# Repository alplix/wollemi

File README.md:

# Wollemi

> **Private for now.** The repository will be opened to the public once the design is complete. No licence has been applied yet; the plan (`docs/licensing.md`) is CERN-OHL-S-2.0 for hardware,
> Apache-2.0 for software and CC-BY-4.0 for documents. Analysis-level design only: no hardware exists, nothing here is qualified for flight, and every number is an engineering estimate.

Wollemi is an open, modular, fully documented small-satellite **platform** and a first mission built on it: a science-first, long-life **12U observatory** with a tiered 50-year survival design.
Everything is generated from configuration files and checked by tools, so a derived mission is a configuration change plus new cards.

*Türkçe özet:* Wollemi, açık kaynak, modüler bir küçük uydu platformu ve üzerine kurulu ilk görev: uzun ömürlü, bilim öncelikli 12U gözlemevi. Tasarım analiz düzeyinde tamamlandı (donanım yok);
her sayı config dosyalarından üretilen araçlarla doğrulanıyor. Depo şimdilik özel, tasarım olgunlaşınca herkese açılacak.

## Where things stand

The design is **complete at analysis level**: requirements, architecture, CAD with interference checks, power/thermal/attitude/orbit/structure analyses, protocol and firmware core with tests,
electronics interface (KiCad, DRC clean), FMEA, test plan, operations concept, cost and schedule. Start with **`docs/sdd.md`** (system design document) and **`docs/status.md`** (latest regression).
What is missing is physical: vendor data, schematics of the functional cards, prototypes, tests, a launch and an operator. See `docs/plan.md`, `docs/risks.md` and `docs/cost.md`.

| At a glance | Value |
|---|---|
| Form | 12U CubeSat envelope, 2 x 2 x 3 cell grid around a central spine, notched 100 x 100 mm cards |
| Mass / power | about 16.8 kg of 24 kg; 58 W sun-biased, 28 W tumbling, 3 W safe-mode load |
| Science | ~26 instruments: telescope (5 m class) + hyperspectral, thermal IR, magnetometer, particles, X-ray/UV, TSI, VLF, GRB, dosimetry, SEU/flash experiments |
| Compute | MSP430 supervisor, 2 x STM32H7, mass memory unit (8 x 128 GB, 6+2), Pi CM5, Jetson Orin Nano |
| Power | two LiFePO4 chains + independent survival chain, hardware-only protection |
| Propulsion | iodine electric thruster on the centre line, ~570 m/s available (about 190 m/s planned), drag sail |
| Verification | 47 requirements traced (see `docs/verification-matrix.md`); most checked automatically on every run; 29 planned tests |

## Documentation

| Topic | Read |
|---|---|
| Overview | `docs/sdd.md`, `docs/plan.md`, `docs/status.md` |
| Requirements and verification | `mission/requirements.md`, `docs/verification-matrix.md`, `docs/test-plan.md`, `docs/fmea.md`, `docs/risks.md` |
| Design | `docs/architecture.md`, `docs/layout.md`, `docs/structure.md`, `docs/icd.md`, `mechanical/README.md` |
| Power, thermal, attitude, propulsion | `docs/power-architecture.md`, `docs/eps-card.md`, `docs/thermal.md`, `docs/adcs.md`, `docs/propulsion.md`, `docs/orbit-and-debris.md` |
| Electronics, software, data | `docs/electrical-interface.md`, `docs/firmware-architecture.md`, `docs/protocol.md`, `docs/data-plan.md`, `docs/mission-simulation.md` |
| Operations and ground | `docs/ops-concept.md`, `docs/ground-station-kit.md`, `docs/longevity.md` |
| Context | `docs/sponsor-brief.md`, `docs/relay-policy.md`, `docs/prior-art.md`, `docs/design-identity.md`, `docs/decisions/`, `docs/outreach-led.md`, `docs/cost.md`, `docs/licensing.md`, `CREDITS.md` |

## Repository layout

| Path | Content |
|---|---|
| `configs/` | Single source of truth: science, geometry, layout, data, longevity, thermal, structure, cost (+ 2U/3U/6U variants) |
| `mission/` | Requirements, `traceability.toml` (requirement -> verification), `tests.toml` (planned tests), `fmea.toml` |
| `sim/` | Budgets, layout rules, balance, data, longevity, link, EPS, ADCS, thermal, structure, orbit lifetime, mission simulation, cost, LED visibility, live verification matrix |
| `mechanical/` | Voxel packing, parametric build123d assembly, interference/mass properties, STEP/STL/renders |
| `electronics/` | Connector pinout (single source), KiCad card template and 15-slot backplane strip (DRC clean), EPS diagram, EPS/survival card floor plans (DRC clean, not yet a schematic) |
| `protocol/` | Message definitions, C/Python/Kaitai Struct generators, tests (round trip, corruption, byte-exact C <-> Python, Kaitai model verified against a real compiler) |
| `firmware/` | Host-testable core: Ed25519 command authentication, modes, FDIR, command queue, A/B OTA (84 unit checks + signature cross-checks) |
| `groundstation/` | Pass prediction, contact plan, reference decoder, Kaitai Struct decoders for the whole protocol |
| `tools/` | `check_all.py` (whole regression), FMEA, test-plan and requirement checks, generators for the ICD and the SDD |
| `site/` | Draft project website (English), prepared but not published -- repository is still private (`site/README.md`) |

## Quick start

```
pip install build123d cryptography sgp4       # CAD kernel, signing tests, orbit propagation (numpy, scipy, pillow come with build123d); KiCad 10 optional for DRC
python tools/check_all.py                     # runs every analysis and test, writes docs/status.md   (--quick skips CAD, thermal and the verification matrix)
python sim/trace_check.py                     # live requirements verification matrix
python mechanical/wollemi_cad.py               # full CAD assembly and checks, exports into mechanical/out/
python tools/gen_sdd.py                       # regenerate the system design document
```

Requires Python 3.11+ and GCC for the firmware and protocol tests. The `sim/` tools use only the standard library unless noted.

## Status and next steps

Design freeze candidate v0 at analysis level. The decisions that shape everything next: choose the target (flight mission, flight-quality reference design, or the precursor path with a FlatSat and a balloon flight),
confirm the preferred orbit, and get vendor quotes and datasheets. Details in `docs/sdd.md` section 8.

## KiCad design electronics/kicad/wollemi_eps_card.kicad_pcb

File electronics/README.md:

# Electronics

| File | Role |
|---|---|
| `card_pinout.toml` | Single source for the WL-P and WL-D connector pinouts and the card outline |
| `gen_card.py` | Generates the KiCad card template and `pinout.md`, runs `kicad-cli` DRC (needs KiCad 10) |
| `kicad/wollemi_card_template.kicad_pcb` | 100 x 100 mm card with the 20 x 20 mm spine notch, 4 x M2.5 holes, edge-guide keep-outs, WL-P and WL-D connector placeholders with every net assigned |
| `kicad/wollemi_card_template.svg`, `_top.png` | Renders |
| `gen_backplane.py` | Generates the 15-slot passive backplane strip (one per column), runs `kicad-cli` DRC |
| `kicad/wollemi_backplane_strip.kicad_pcb` | Passive backplane strip: 15 card slots, WL-P/WL-D routing per chain, DRC clean |
| `gen_eps_card.py` | Generates function-block floor plans for the EPS-A/EPS-B and survival cards on the real card outline (`docs/eps-card.md`), runs `kicad-cli` DRC |
| `kicad/wollemi_eps_card.kicad_pcb`, `wollemi_survival_card.kicad_pcb` | Floor plans only: labelled placeholder blocks proving the partition fits the card, DRC clean; not a routed schematic |
| `eps_diagram.py` | Generates the EPS block diagram `eps_diagram.svg` |
| `pinout.md` | Generated pin tables |

```
python electronics/gen_card.py
python electronics/gen_backplane.py
python electronics/gen_eps_card.py
```

The card template has no routing yet: `unconnected_items` and generated-library warnings are silenced in its project file on purpose. Cards derived
from it must re-enable them. Connector footprints are placeholders (2-row, 1.27 mm pitch pads); replace with the vendor footprint once the
connector family is chosen (`docs/electrical-interface.md`).

Next: choose real parts and capture a routed schematic for the EPS and survival cards (`docs/eps-card.md`); a first functional (non-EPS) card schematic.

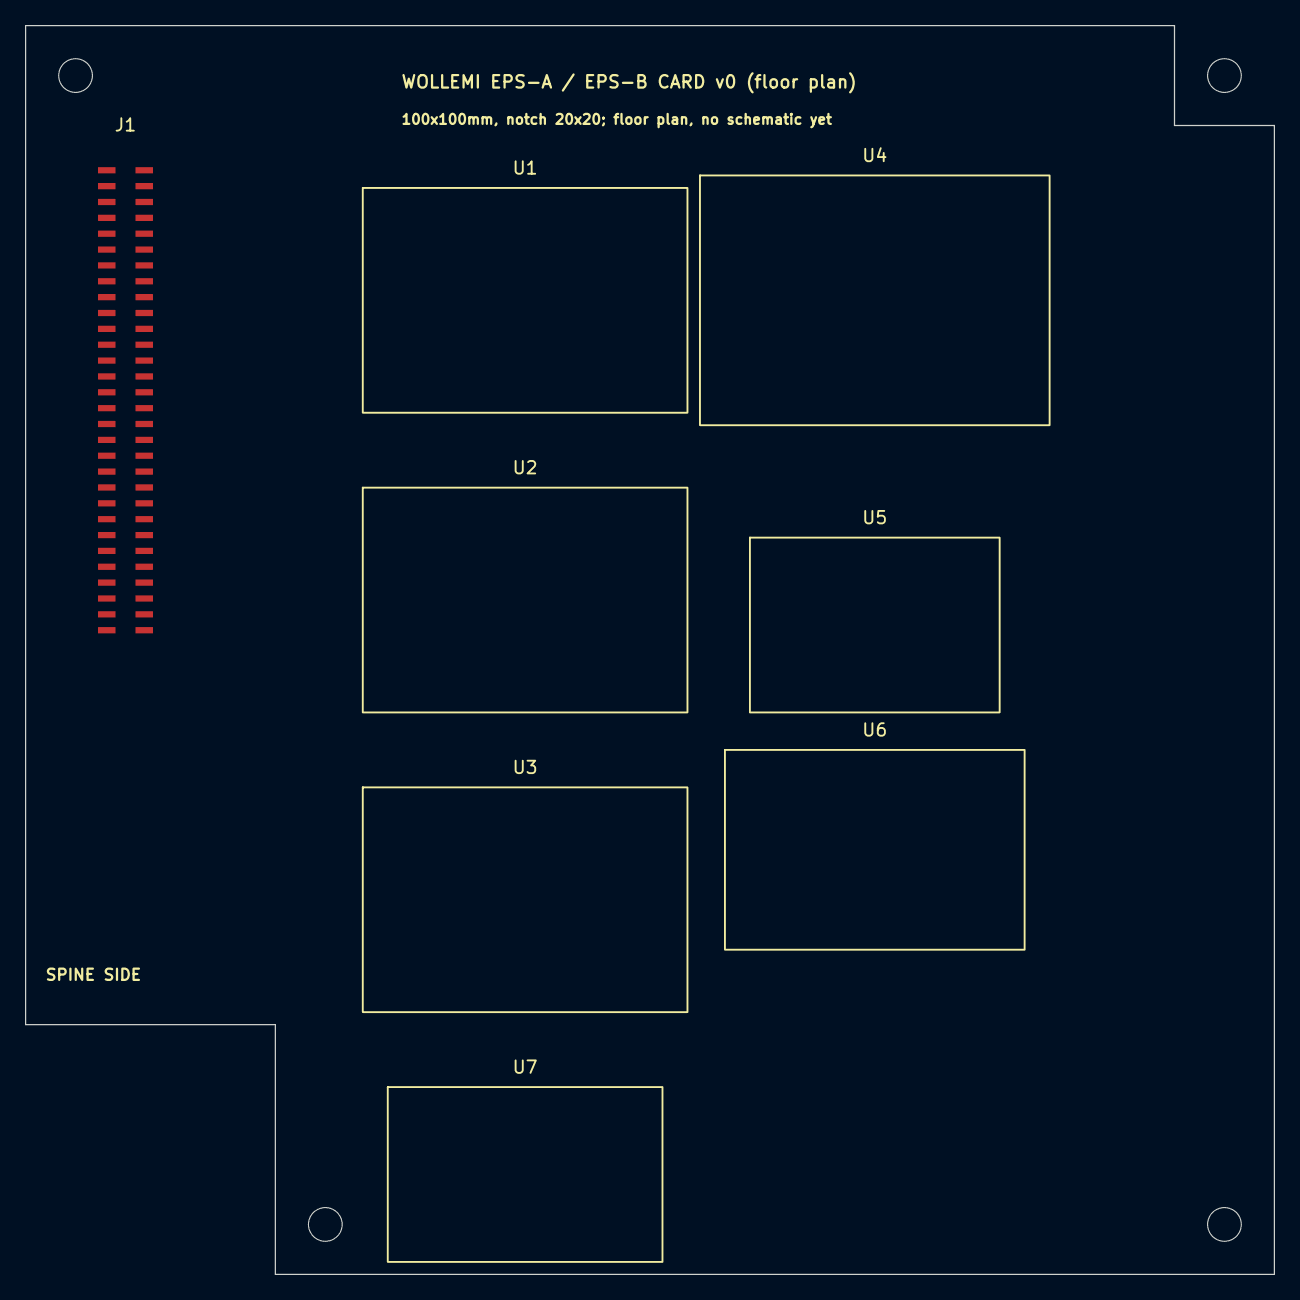
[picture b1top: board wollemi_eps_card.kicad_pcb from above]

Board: 4 copper layers, 100.0 x 100.0 mm, 12 parts (0 on the bottom side), 4 nets, no tracks yet.

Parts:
H: M2.5; MountingHole_2.7mm_M2.5
H#2, H#3, H#4: M2.5; MountingHole_2.7mm_M2.5
J1: WL-P; WL-P_placeholder
U1, U2, U3: LT8490; LT8490_placeholder
U4: BQ29209-Q1; BQ29209-Q1_placeholder
U5: LTC4359; LTC4359_placeholder
U6: TPS2597x; TPS2597x_placeholder
U7: STM32G0B1; STM32G0B1_placeholder

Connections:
GND: J1.11, J1.12, J1.15, J1.16, J1.19, J1.20, J1.23, J1.24, J1.27, J1.28, J1.39, J1.40, J1.45, J1.46, J1.51, J1.52
RSV: J1.54, J1.55, J1.56, J1.57, J1.58, J1.59, J1.60
VBAT_A: J1.1, J1.3, J1.5, J1.7, J1.9
VBAT_B: J1.2, J1.4, J1.6, J1.8, J1.10

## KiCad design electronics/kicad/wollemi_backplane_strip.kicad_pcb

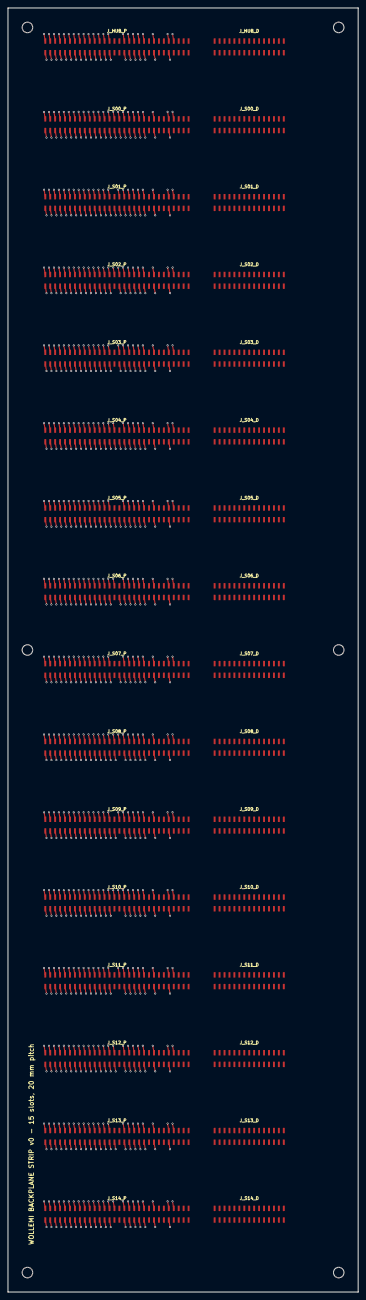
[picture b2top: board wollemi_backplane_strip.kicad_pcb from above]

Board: 6 copper layers, 90.0 x 330.0 mm, 38 parts (0 on the bottom side), 20 nets.

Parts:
H: M2.5; MountingHole_2.7mm_M2.5
H#2, H#3, H#4, H#5, H#6: M2.5; MountingHole_2.7mm_M2.5
J_HUB_D: WL-D; WL-D_backplane_placeholder
J_HUB_P: WL-P; WL-P_backplane_placeholder
J_S00_D, J_S01_D, J_S02_D, J_S03_D, J_S04_D, J_S05_D, J_S06_D, J_S07_D, J_S08_D, J_S09_D, J_S10_D, J_S11_D, J_S12_D, J_S13_D, J_S14_D: WL-D; WL-D_backplane_placeholder
J_S00_P, J_S01_P, J_S02_P, J_S03_P, J_S04_P, J_S05_P, J_S06_P, J_S07_P, J_S08_P, J_S09_P, J_S10_P, J_S11_P, J_S12_P, J_S13_P, J_S14_P: WL-P; WL-P_backplane_placeholder

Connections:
CAN_A_H: J_HUB_P.13, J_S00_P.13, J_S01_P.13, J_S02_P.13, J_S03_P.13, J_S04_P.13, J_S05_P.13, J_S06_P.13, J_S07_P.13, J_S08_P.13, J_S09_P.13, J_S10_P.13, J_S11_P.13, J_S12_P.13, J_S13_P.13, J_S14_P.13
CAN_A_L: J_HUB_P.14, J_S00_P.14, J_S01_P.14, J_S02_P.14, J_S03_P.14, J_S04_P.14, J_S05_P.14, J_S06_P.14, J_S07_P.14, J_S08_P.14, J_S09_P.14, J_S10_P.14, J_S11_P.14, J_S12_P.14, J_S13_P.14, J_S14_P.14
CAN_B_H: J_HUB_P.17, J_S00_P.17, J_S01_P.17, J_S02_P.17, J_S03_P.17, J_S04_P.17, J_S05_P.17, J_S06_P.17, J_S07_P.17, J_S08_P.17, J_S09_P.17, J_S10_P.17, J_S11_P.17, J_S12_P.17, J_S13_P.17, J_S14_P.17
CAN_B_L: J_HUB_P.18, J_S00_P.18, J_S01_P.18, J_S02_P.18, J_S03_P.18, J_S04_P.18, J_S05_P.18, J_S06_P.18, J_S07_P.18, J_S08_P.18, J_S09_P.18, J_S10_P.18, J_S11_P.18, J_S12_P.18, J_S13_P.18, J_S14_P.18
FAULT_N: J_HUB_P.38, J_S00_P.38, J_S01_P.38, J_S02_P.38, J_S03_P.38, J_S04_P.38, J_S05_P.38, J_S06_P.38, J_S07_P.38, J_S08_P.38, J_S09_P.38, J_S10_P.38, J_S11_P.38, J_S12_P.38, J_S13_P.38, J_S14_P.38
GND: J_HUB_P.11, J_HUB_P.12, J_HUB_P.15, J_HUB_P.16, J_HUB_P.19, J_HUB_P.20, J_HUB_P.23, J_HUB_P.24, J_HUB_P.27, J_HUB_P.28, J_HUB_P.39, J_HUB_P.40, J_HUB_P.45, J_HUB_P.46, J_HUB_P.51, J_HUB_P.52, J_S00_P.11, J_S00_P.12, J_S00_P.15, J_S00_P.16, J_S00_P.19, J_S00_P.20, J_S00_P.23, J_S00_P.24, J_S00_P.27, J_S00_P.28, J_S00_P.29, J_S00_P.30, J_S00_P.31, J_S00_P.32, J_S00_P.39, J_S00_P.40, J_S00_P.45, J_S00_P.46, J_S00_P.51, J_S00_P.52, J_S01_P.11, J_S01_P.12, J_S01_P.15, J_S01_P.16, J_S01_P.19, J_S01_P.20, J_S01_P.23, J_S01_P.24, J_S01_P.27, J_S01_P.28, J_S01_P.30, J_S01_P.31, J_S01_P.32, J_S01_P.39, J_S01_P.40, J_S01_P.45, J_S01_P.46, J_S01_P.51, J_S01_P.52, J_S02_P.11, J_S02_P.12, J_S02_P.15, J_S02_P.16, J_S02_P.19, J_S02_P.20, J_S02_P.23, J_S02_P.24, J_S02_P.27, J_S02_P.28, J_S02_P.29, J_S02_P.31, J_S02_P.32, J_S02_P.39, J_S02_P.40, J_S02_P.45, J_S02_P.46, J_S02_P.51, J_S02_P.52, J_S03_P.11, J_S03_P.12, J_S03_P.15, J_S03_P.16, J_S03_P.19, J_S03_P.20, J_S03_P.23, J_S03_P.24, J_S03_P.27, J_S03_P.28, J_S03_P.31, J_S03_P.32, J_S03_P.39, J_S03_P.40, J_S03_P.45, J_S03_P.46, J_S03_P.51, J_S03_P.52, J_S04_P.11, J_S04_P.12, J_S04_P.15, J_S04_P.16, J_S04_P.19, J_S04_P.20, J_S04_P.23, J_S04_P.24, J_S04_P.27, J_S04_P.28, J_S04_P.29, J_S04_P.30, J_S04_P.32, J_S04_P.39, J_S04_P.40, J_S04_P.45, J_S04_P.46, J_S04_P.51, J_S04_P.52, J_S05_P.11, J_S05_P.12, J_S05_P.15, J_S05_P.16, J_S05_P.19, J_S05_P.20, J_S05_P.23, J_S05_P.24, J_S05_P.27, J_S05_P.28, J_S05_P.30, J_S05_P.32, J_S05_P.39, J_S05_P.40, J_S05_P.45, J_S05_P.46, J_S05_P.51, J_S05_P.52, J_S06_P.11, J_S06_P.12, J_S06_P.15, J_S06_P.16, J_S06_P.19, J_S06_P.20, J_S06_P.23, J_S06_P.24, J_S06_P.27, J_S06_P.28, J_S06_P.29, J_S06_P.32, J_S06_P.39, J_S06_P.40, J_S06_P.45, J_S06_P.46, J_S06_P.51, J_S06_P.52, J_S07_P.11, J_S07_P.12, J_S07_P.15, J_S07_P.16, J_S07_P.19, J_S07_P.20, J_S07_P.23, J_S07_P.24, J_S07_P.27, J_S07_P.28, J_S07_P.32, J_S07_P.39, J_S07_P.40, J_S07_P.45, J_S07_P.46, J_S07_P.51, J_S07_P.52, J_S08_P.11, J_S08_P.12, J_S08_P.15, J_S08_P.16, J_S08_P.19, J_S08_P.20, J_S08_P.23, J_S08_P.24, J_S08_P.27, J_S08_P.28, J_S08_P.29, J_S08_P.30, J_S08_P.31, J_S08_P.39, J_S08_P.40, J_S08_P.45, J_S08_P.46, J_S08_P.51, J_S08_P.52, J_S09_P.11, J_S09_P.12, J_S09_P.15, J_S09_P.16, J_S09_P.19, J_S09_P.20, J_S09_P.23, J_S09_P.24, J_S09_P.27, J_S09_P.28, J_S09_P.30, J_S09_P.31, J_S09_P.39, J_S09_P.40, J_S09_P.45, J_S09_P.46, J_S09_P.51, J_S09_P.52, J_S10_P.11, J_S10_P.12, J_S10_P.15, J_S10_P.16, J_S10_P.19, J_S10_P.20, J_S10_P.23, J_S10_P.24, J_S10_P.27, J_S10_P.28, J_S10_P.29, J_S10_P.31, J_S10_P.39, J_S10_P.40, J_S10_P.45, J_S10_P.46, J_S10_P.51, J_S10_P.52, J_S11_P.11, J_S11_P.12, J_S11_P.15, J_S11_P.16, J_S11_P.19, J_S11_P.20, J_S11_P.23, J_S11_P.24, J_S11_P.27, J_S11_P.28, J_S11_P.31, J_S11_P.39, J_S11_P.40, J_S11_P.45, J_S11_P.46, J_S11_P.51, J_S11_P.52, J_S12_P.11, J_S12_P.12, J_S12_P.15, J_S12_P.16, J_S12_P.19, J_S12_P.20, J_S12_P.23, J_S12_P.24, J_S12_P.27, J_S12_P.28, J_S12_P.29, J_S12_P.30, J_S12_P.39, J_S12_P.40, J_S12_P.45, J_S12_P.46, J_S12_P.51, J_S12_P.52, J_S13_P.11, J_S13_P.12, J_S13_P.15, J_S13_P.16, J_S13_P.19, J_S13_P.20, J_S13_P.23, J_S13_P.24, J_S13_P.27, J_S13_P.28, J_S13_P.30, J_S13_P.39, J_S13_P.40, J_S13_P.45, J_S13_P.46, J_S13_P.51, J_S13_P.52, J_S14_P.11, J_S14_P.12, J_S14_P.15, J_S14_P.16, J_S14_P.19, J_S14_P.20, J_S14_P.23, J_S14_P.24, J_S14_P.27, J_S14_P.28, J_S14_P.29, J_S14_P.39, J_S14_P.40, J_S14_P.45, J_S14_P.46, J_S14_P.51, J_S14_P.52
I2C_SCL: J_HUB_P.41, J_S00_P.41, J_S01_P.41, J_S02_P.41, J_S03_P.41, J_S04_P.41, J_S05_P.41, J_S06_P.41, J_S07_P.41, J_S08_P.41, J_S09_P.41, J_S10_P.41, J_S11_P.41, J_S12_P.41, J_S13_P.41, J_S14_P.41
I2C_SDA: J_HUB_P.42, J_S00_P.42, J_S01_P.42, J_S02_P.42, J_S03_P.42, J_S04_P.42, J_S05_P.42, J_S06_P.42, J_S07_P.42, J_S08_P.42, J_S09_P.42, J_S10_P.42, J_S11_P.42, J_S12_P.42, J_S13_P.42, J_S14_P.42
KILL_N: J_HUB_P.37, J_S00_P.37, J_S01_P.37, J_S02_P.37, J_S03_P.37, J_S04_P.37, J_S05_P.37, J_S06_P.37, J_S07_P.37, J_S08_P.37, J_S09_P.37, J_S10_P.37, J_S11_P.37, J_S12_P.37, J_S13_P.37, J_S14_P.37
PPS_N: J_HUB_P.22, J_S00_P.22, J_S01_P.22, J_S02_P.22, J_S03_P.22, J_S04_P.22, J_S05_P.22, J_S06_P.22, J_S07_P.22, J_S08_P.22, J_S09_P.22, J_S10_P.22, J_S11_P.22, J_S12_P.22, J_S13_P.22, J_S14_P.22
PPS_P: J_HUB_P.21, J_S00_P.21, J_S01_P.21, J_S02_P.21, J_S03_P.21, J_S04_P.21, J_S05_P.21, J_S06_P.21, J_S07_P.21, J_S08_P.21, J_S09_P.21, J_S10_P.21, J_S11_P.21, J_S12_P.21, J_S13_P.21, J_S14_P.21
RESET_N: J_HUB_P.53, J_S00_P.53, J_S01_P.53, J_S02_P.53, J_S03_P.53, J_S04_P.53, J_S05_P.53, J_S06_P.53, J_S07_P.53, J_S08_P.53, J_S09_P.53, J_S10_P.53, J_S11_P.53, J_S12_P.53, J_S13_P.53, J_S14_P.53
SLOT_SEL0: J_HUB_P.33, J_S00_P.33, J_S01_P.33, J_S02_P.33, J_S03_P.33, J_S04_P.33, J_S05_P.33, J_S06_P.33, J_S07_P.33, J_S08_P.33, J_S09_P.33, J_S10_P.33, J_S11_P.33, J_S12_P.33, J_S13_P.33, J_S14_P.33
SLOT_SEL1: J_HUB_P.34, J_S00_P.34, J_S01_P.34, J_S02_P.34, J_S03_P.34, J_S04_P.34, J_S05_P.34, J_S06_P.34, J_S07_P.34, J_S08_P.34, J_S09_P.34, J_S10_P.34, J_S11_P.34, J_S12_P.34, J_S13_P.34, J_S14_P.34
SLOT_SEL2: J_HUB_P.35, J_S00_P.35, J_S01_P.35, J_S02_P.35, J_S03_P.35, J_S04_P.35, J_S05_P.35, J_S06_P.35, J_S07_P.35, J_S08_P.35, J_S09_P.35, J_S10_P.35, J_S11_P.35, J_S12_P.35, J_S13_P.35, J_S14_P.35
SLOT_SEL3: J_HUB_P.36, J_S00_P.36, J_S01_P.36, J_S02_P.36, J_S03_P.36, J_S04_P.36, J_S05_P.36, J_S06_P.36, J_S07_P.36, J_S08_P.36, J_S09_P.36, J_S10_P.36, J_S11_P.36, J_S12_P.36, J_S13_P.36, J_S14_P.36
SYNC_N: J_HUB_P.26, J_S00_P.26, J_S01_P.26, J_S02_P.26, J_S03_P.26, J_S04_P.26, J_S05_P.26, J_S06_P.26, J_S07_P.26, J_S08_P.26, J_S09_P.26, J_S10_P.26, J_S11_P.26, J_S12_P.26, J_S13_P.26, J_S14_P.26
SYNC_P: J_HUB_P.25, J_S00_P.25, J_S01_P.25, J_S02_P.25, J_S03_P.25, J_S04_P.25, J_S05_P.25, J_S06_P.25, J_S07_P.25, J_S08_P.25, J_S09_P.25, J_S10_P.25, J_S11_P.25, J_S12_P.25, J_S13_P.25, J_S14_P.25
VBAT_A: J_HUB_P.1, J_HUB_P.3, J_HUB_P.5, J_HUB_P.7, J_HUB_P.9, J_S00_P.1, J_S00_P.3, J_S00_P.5, J_S00_P.7, J_S00_P.9, J_S01_P.1, J_S01_P.3, J_S01_P.5, J_S01_P.7, J_S01_P.9, J_S02_P.1, J_S02_P.3, J_S02_P.5, J_S02_P.7, J_S02_P.9, J_S03_P.1, J_S03_P.3, J_S03_P.5, J_S03_P.7, J_S03_P.9, J_S04_P.1, J_S04_P.3, J_S04_P.5, J_S04_P.7, J_S04_P.9, J_S05_P.1, J_S05_P.3, J_S05_P.5, J_S05_P.7, J_S05_P.9, J_S06_P.1, J_S06_P.3, J_S06_P.5, J_S06_P.7, J_S06_P.9, J_S07_P.1, J_S07_P.3, J_S07_P.5, J_S07_P.7, J_S07_P.9, J_S08_P.1, J_S08_P.3, J_S08_P.5, J_S08_P.7, J_S08_P.9, J_S09_P.1, J_S09_P.3, J_S09_P.5, J_S09_P.7, J_S09_P.9, J_S10_P.1, J_S10_P.3, J_S10_P.5, J_S10_P.7, J_S10_P.9, J_S11_P.1, J_S11_P.3, J_S11_P.5, J_S11_P.7, J_S11_P.9, J_S12_P.1, J_S12_P.3, J_S12_P.5, J_S12_P.7, J_S12_P.9, J_S13_P.1, J_S13_P.3, J_S13_P.5, J_S13_P.7, J_S13_P.9, J_S14_P.1, J_S14_P.3, J_S14_P.5, J_S14_P.7, J_S14_P.9
VBAT_B: J_HUB_P.2, J_HUB_P.4, J_HUB_P.6, J_HUB_P.8, J_HUB_P.10, J_S00_P.2, J_S00_P.4, J_S00_P.6, J_S00_P.8, J_S00_P.10, J_S01_P.2, J_S01_P.4, J_S01_P.6, J_S01_P.8, J_S01_P.10, J_S02_P.2, J_S02_P.4, J_S02_P.6, J_S02_P.8, J_S02_P.10, J_S03_P.2, J_S03_P.4, J_S03_P.6, J_S03_P.8, J_S03_P.10, J_S04_P.2, J_S04_P.4, J_S04_P.6, J_S04_P.8, J_S04_P.10, J_S05_P.2, J_S05_P.4, J_S05_P.6, J_S05_P.8, J_S05_P.10, J_S06_P.2, J_S06_P.4, J_S06_P.6, J_S06_P.8, J_S06_P.10, J_S07_P.2, J_S07_P.4, J_S07_P.6, J_S07_P.8, J_S07_P.10, J_S08_P.2, J_S08_P.4, J_S08_P.6, J_S08_P.8, J_S08_P.10, J_S09_P.2, J_S09_P.4, J_S09_P.6, J_S09_P.8, J_S09_P.10, J_S10_P.2, J_S10_P.4, J_S10_P.6, J_S10_P.8, J_S10_P.10, J_S11_P.2, J_S11_P.4, J_S11_P.6, J_S11_P.8, J_S11_P.10, J_S12_P.2, J_S12_P.4, J_S12_P.6, J_S12_P.8, J_S12_P.10, J_S13_P.2, J_S13_P.4, J_S13_P.6, J_S13_P.8, J_S13_P.10, J_S14_P.2, J_S14_P.4, J_S14_P.6, J_S14_P.8, J_S14_P.10

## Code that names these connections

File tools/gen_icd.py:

"""Generate docs/icd.md (interface control document) from the live design data.

Usage: python tools/gen_icd.py
Every number in the tables is read from the configs or computed by the analysis tools, so the ICD cannot drift from the design.
"""
import json
import os
import sys
import tomllib

ROOT = os.path.dirname(os.path.dirname(os.path.abspath(__file__)))
sys.path.insert(0, os.path.join(ROOT, "sim"))
sys.path.insert(0, os.path.join(ROOT, "mechanical"))
import budget  # noqa: E402
import wollemi_cad as gc  # noqa: E402


def load(p):
    return tomllib.load(open(os.path.join(ROOT, p), "rb"))


def main():
    cfg = load("configs/12u_science.toml")
    geo = load("configs/12u_geometry.toml")
    st = load("configs/12u_structure.toml")
    data = load("configs/12u_data.toml")
    pin = load("electronics/card_pinout.toml")
    placement = json.load(open(os.path.join(ROOT, "mechanical", "out", "placement.json")))
    r = budget.compute(cfg)
    M, com, inertia = gc.mass_props(placement["placed"], cfg, False, geo)
    Md, comd, inertia_d = gc.mass_props(placement["placed"], cfg, True, geo)
    fr = geo["frame"]
    wg = geo["wings"]
    ox, oy, oz = fr["outer"]
    stack = wg["panels_per_wing"] * wg["panel"][2]
    span = 2 * (ox / 2 + wg["panels_per_wing"] * wg["panel"][0])
    safe = next(s for s in r["scenarios"] if s["safe"])["cons"]
    n_gkp = len(pin["gkp"]["pairs"]) * 2
    n_gkd = len(pin["gkd"]["pairs"]) * 2
    link = data["link"]

    L = []
    a = L.append
    a("# Interface control document (generated)")
    a("")
    a("Generated by `python tools/gen_icd.py` from the configs and analysis tools; do not edit by hand. Every value is a design value (analysis or estimate) unless a source is named;")
    a("the launch-provider values in section 6 are assumptions to be replaced by the provider's interface requirements document.")
    a("")
    a("## 1. Mechanical interfaces")
    a("")
    a("| Item | Value | Source |")
    a("|---|---|---|")
    a(f"| Form factor | 12U CubeSat, envelope {ox:.1f} x {oy:.1f} x {oz:.1f} mm, rails {fr['rail']} mm | `configs/12u_geometry.toml` |")
    a(f"| Mass at launch | {r['mass_kg']:.2f} kg (limit 24 kg) | `sim/budget.py` |")
    a(f"| Centre of mass (offset from the geometric centre) | ({com[0]:+.1f}, {com[1]:+.1f}, {com[2]:+.1f}) mm stowed; ({comd[0]:+.1f}, {comd[1]:+.1f}, {comd[2]:+.1f}) mm wings deployed | `mechanical/wollemi_cad.py` |")
    a(f"| Moments of inertia (kg m2) | stowed ({inertia[0]:.3f}, {inertia[1]:.3f}, {inertia[2]:.3f}); deployed ({inertia_d[0]:.3f}, {inertia_d[1]:.3f}, {inertia_d[2]:.3f}) | same |")
    a(f"| Stowed wing stack thickness | {stack:.1f} mm (allowed protrusion {fr['protrusion_limit']} mm), six hold-down posts per wing | `docs/structure.md` |")
    a(f"| External protrusions | patch antennas 4 mm; thruster nozzle flush; boom and UHF antenna stowed inside the envelope | CAD |")
    a(f"| Deployables | 2 wings x {wg['panels_per_wing']} panels ({wg['panel'][0]:.0f} x {wg['panel'][1]:.0f} x {wg['panel'][2]} mm, cells both faces), deployed span {span:.0f} mm; magnetometer boom and UHF antenna (lengths to be fixed) | CAD |")
    a(f"| Internal architecture | 2 x 2 x 3 cell grid, central spine 40 mm, notched card 100 x 100 mm (20 mm notch, 8 mm relief), 4 mm backplane gap | `docs/layout.md`, `docs/electrical-interface.md` |")
    a(f"| Number of modules | {len(placement['placed'])} placed with 0 interferences | CAD check |")
    a("")
    a("## 2. Electrical interfaces")
    a("")
    a("| Item | Value |")
    a("|---|---|")
    a("| Main bus | VBAT_A and VBAT_B, 2S LiFePO4 5.0 - 7.3 V (nominal 6.4 V); cards accept 4.5 - 8.6 V; every card has its own eFuse (trip 1.5x nominal) |")
    a(f"| Card connectors | WL-P {n_gkp} pins (power, CAN-FD A/B, PPS, SYNC, SLOT_ID, SLOT_SEL, KILL_N, FAULT_N, RESET_N, I2C, UART, SWD) and WL-D {n_gkd} pins (Ethernet, fast lanes), pitch {pin['card']['connector_pitch']} mm |")
    a("| Backplane | 15 slots plus hub per column, bussed signals daisy-chained, GND and battery planes (`electronics/gen_backplane.py`, DRC clean) |")
    a("| Battery packs | A and B: 2S2P 26650 LiFePO4, 42 Wh each; C: 5 Wh survival pack with independent charger |")
    a(f"| Solar | wings: 6 panels x 20 cells (10s2p), Vmp ~24 V, ~24 W each; body cells 0.267 m2 usable; survival string 4s2p |")
    a(f"| Power by scenario | full loads {r['consumed_w']:.1f} W average, safe mode {safe:.1f} W, burn mode 53 W (`docs/mission-simulation.md`) |")
    a("| Separation and inhibits | three independent inhibits (timer, supervisor, separation switch); remove-before-flight pin; no RF emission and no deployment until at least 30 minutes after separation (typical rideshare rule, to confirm) |")
    a("| Ground access | umbilical/charge and data port on a rail-accessible connector (design item, not yet detailed) |")
    a("")
    a("## 3. Data and command interfaces")
    a("")
    a("| Item | Value |")
    a("|---|---|")
    a("| Packet format | CCSDS Space Packet with Wollemi secondary header, CRC-16, signed telecommands (Ed25519), 27 messages (`docs/protocol-messages.md`) |")
    a("| Onboard buses | CAN-FD A and B control plane; Gigabit Ethernet data plane between the Linux computers, MMU and the S-band modem |")
    a(f"| UHF | 433 MHz amateur band, LoRa/AX.25 beacon and commands, about {link['uhf_rate_bps'] / 1000:.0f} kbps |")
    a(f"| S-band | 2.4 GHz amateur band, {link['sband_rate_bps'] / 1e6:.1f} Mbps design rate (250 kbps - 2 Mbps adaptive), efficiency {link['link_efficiency']} |")
    a(f"| Reference ground station | Pamukkale (37.9 N, 29.1 E): {link['passes_per_station_day']} passes/day of {link['pass_s']} s |")
    a("| Data products | CFDP file transfer, `.wpk` archive files and JSON index (`docs/protocol.md`) |")
    a("")
    a("## 4. Thermal interfaces")
    a("")
    a("| Item | Value |")
    a("|---|---|")
    a("| Effective face emissivity | about 0.5 (cells plus MLI patches); telescope column faces alpha 0.2 / eps 0.3 (`configs/12u_thermal.toml`) |")
    a("| Predicted ranges | electronics -10 to +33 C, battery 4 to 15 C, telescope column 13 to 25 C in nominal and eclipse orbits (`docs/thermal.md`) |")
    a("| Heaters | battery 6 W thermostat (4/9 C), telescope column 8 W (14/17 C), survival heaters 2 W |")
    a("| Conduction path | column bulkheads and spine; propulsion bay isolated; dispenser contact through the rails only |")
    a("")
    a("## 5. Structural and environmental design levels")
    a("")
    la = st["launch"]
    a("| Item | Value |")
    a("|---|---|")
    a(f"| Quasi-static design load | {la['quasi_static_g']:.0f} g all axes (local amplification {la['local_amplification']:.0f}x) |")
    a(f"| Random vibration | flat {la['random_asd_g2_per_hz']} g2/Hz, 20-2000 Hz (8.9 Grms) |")
    a(f"| Minimum first mode | {la['minimum_first_mode_hz']:.0f} Hz (estimated frame ~900 Hz, wall panels ~170 Hz, stowed wing ~190 Hz with mid posts) |")
    a("| Radiation | TID target 30 krad for the control electronics with the vault; COTS compute treated as consumables (`docs/longevity.md`) |")
    a("")
    a("## 6. Launch and dispenser interface (assumptions)")
    a("")
    a("| Item | Assumption |")
    a("|---|---|")
    a("| Dispenser | 12U rail-type dispenser compatible with the CubeSat Design Specification rails; contact only on the rails |")
    a("| Orbit | dawn-dusk sun-synchronous, about 700 km (preferred); lifetime and disposal in `docs/orbit-and-debris.md` |")
    a("| Loads | provider's specification replaces the design levels above |")
    a("| Materials | outgassing-screened (TML < 1 %, CVCM < 0.1 %); no ahead-of-time pressurised vessels (iodine is a solid at low pressure); battery safety data package required |")
    a("| Regulatory | frequency coordination and licensing before launch, operator of record (`mission/requirements.md`, REG-1, COLAV-1) |")
    a("")
    a("## 7. Open interface items")
    a("")
    a("- Fix the lengths and deployment mechanisms of the magnetometer boom and the UHF antenna; add them to the CAD model.")
    a("- Define the umbilical connector, RBF pin and separation-switch locations on the rails.")
    a("- Replace assumptions in section 6 with the provider's interface requirements document.")
    a("- Vendor CAD and datasheets for the thruster, telescope optics and wheels; update the module envelopes and the electrical current limits.")
    open(os.path.join(ROOT, "docs", "icd.md"), "w", encoding="utf-8").write("\n".join(L) + "\n")
    print("wrote docs/icd.md")


if __name__ == "__main__":
    main()
